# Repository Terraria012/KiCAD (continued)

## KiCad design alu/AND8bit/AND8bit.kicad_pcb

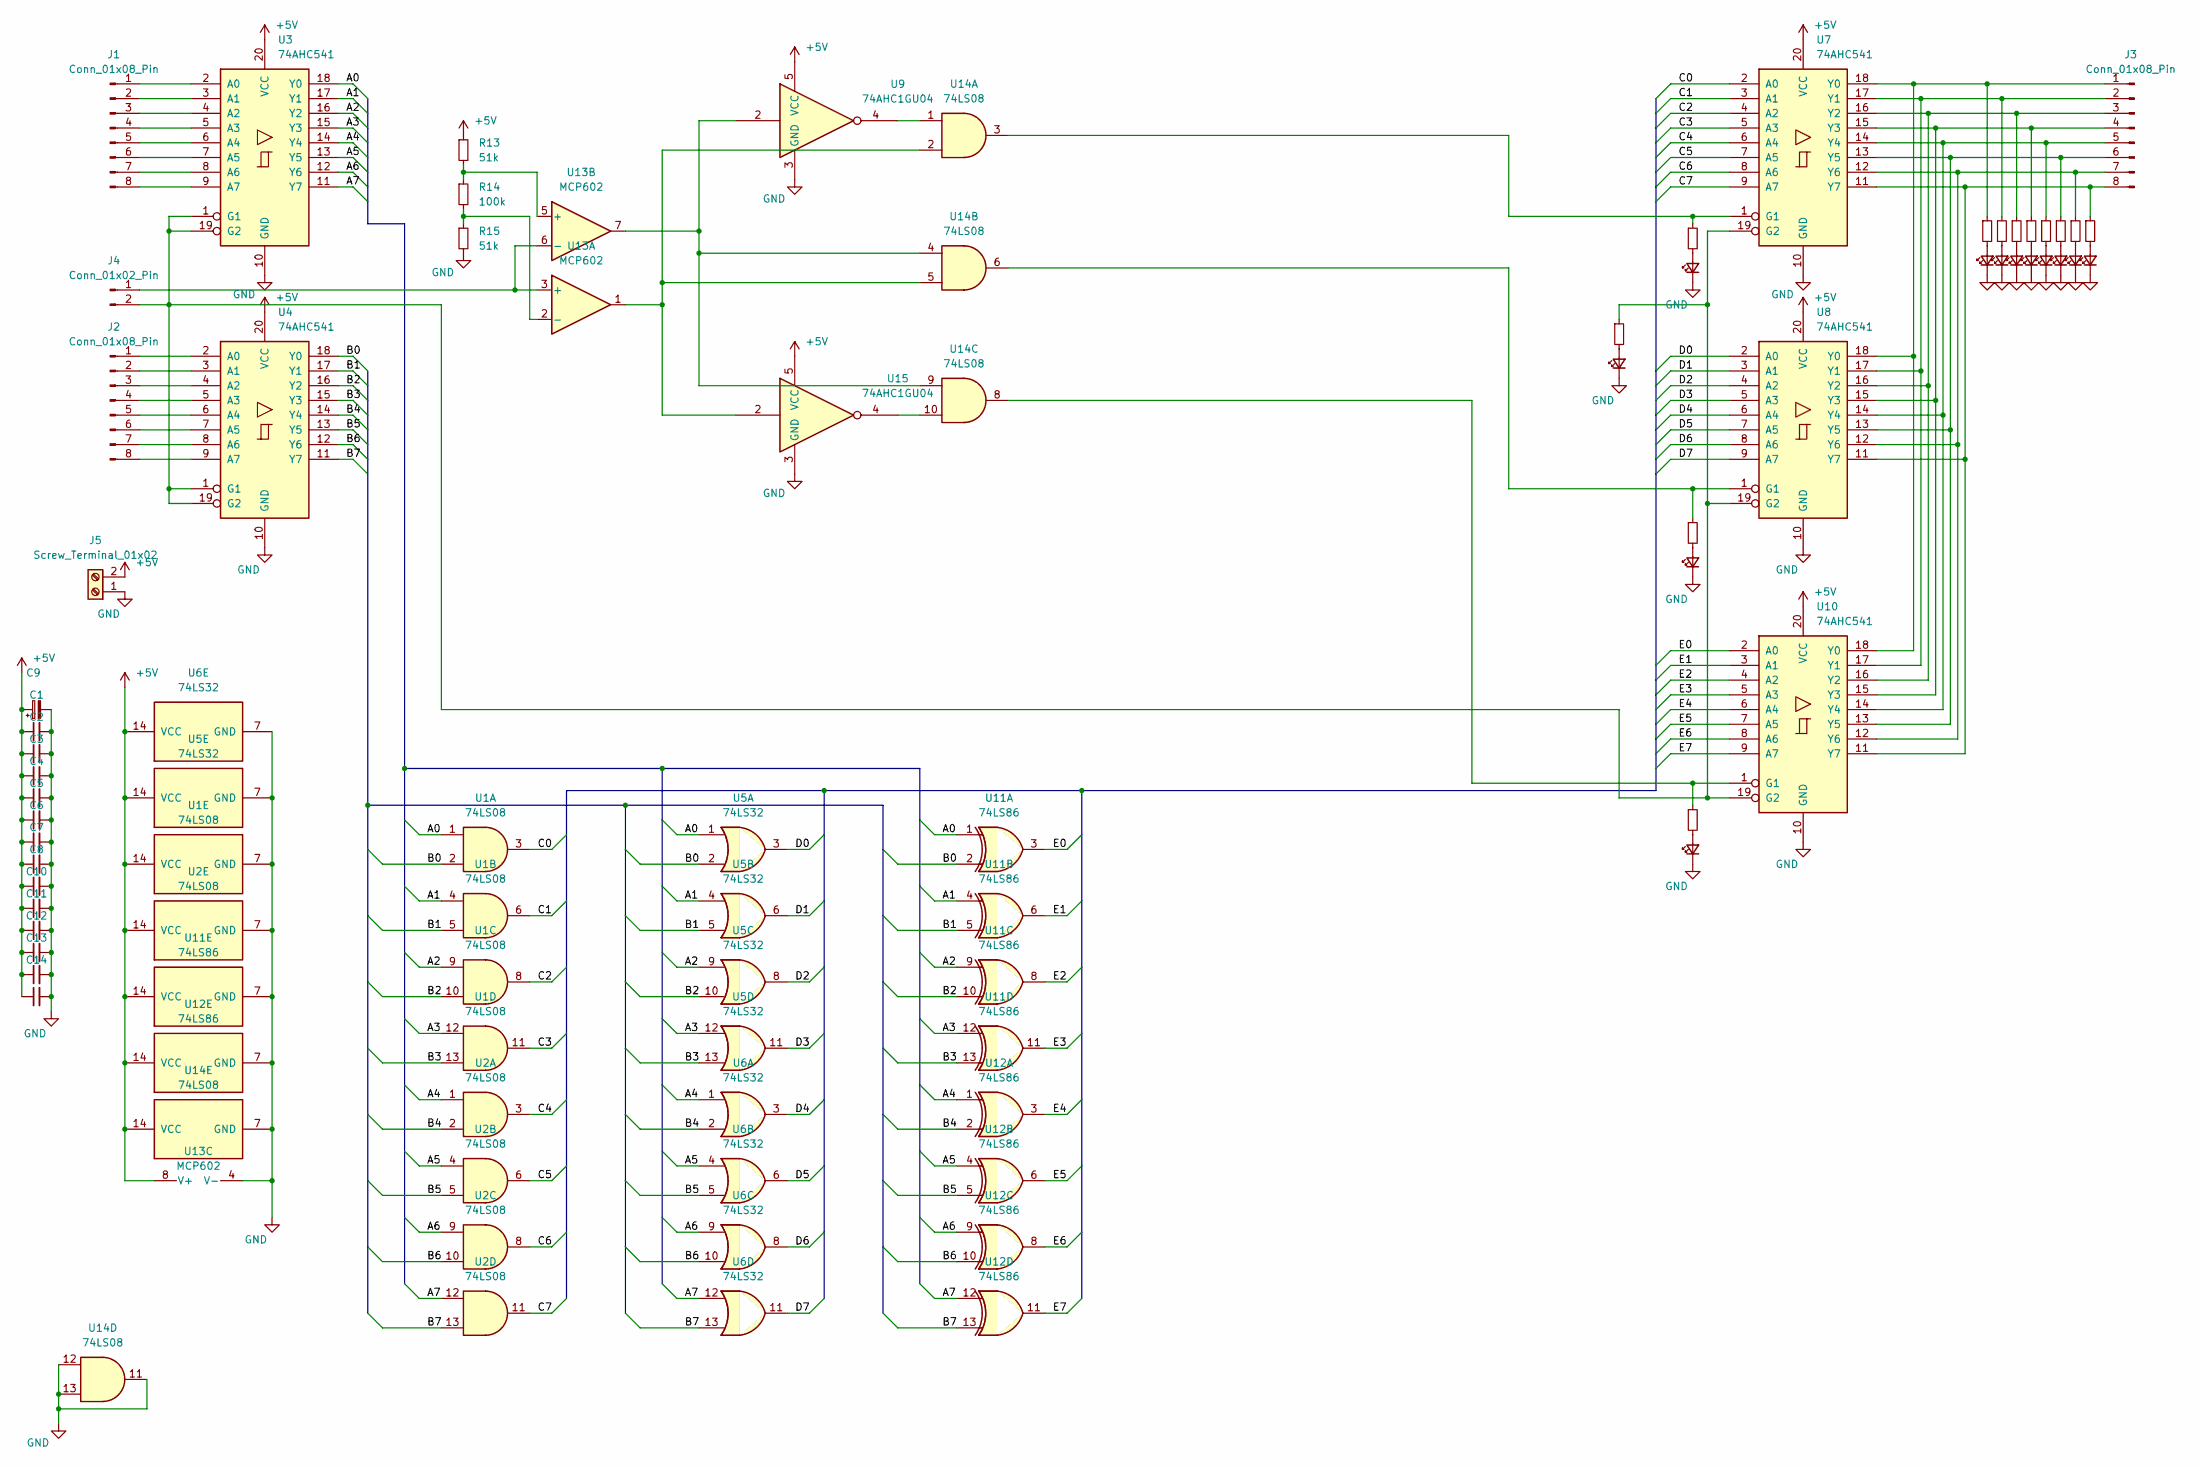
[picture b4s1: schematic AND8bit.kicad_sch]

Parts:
C1, C2, C3, C4, C5, C6, C7, C8, C10, C11, C12, C13, C14: C_Small; C_0603_1608Metric
C9: C_Polarized_Small; CP_Radial_D6.3mm_P2.50mm
D1, D2, D3, D4, D5, D6, D7, D8, D9, D10, D11, D12: LED_Small; LED_0603_1608Metric
J1, J2, J3: Conn_01x08_Pin; PinHeader_1x08_P2.54mm_Vertical
J4: Conn_01x02_Pin; PinHeader_1x02_P2.54mm_Vertical
J5: Screw_Terminal_01x02; TerminalBlock_bornier-2_P5.08mm
R1, R2, R3, R4, R5, R6, R7, R8, R9, R10, R11, R12: R_Small; R_0603_1608Metric
R13, R15: 51k; R_0603_1608Metric
R14: 100k; R_0603_1608Metric
U1, U2, U14: 74LS08; DIP-14_W7.62mm
U3, U4, U7, U8, U10: 74AHC541; DIP-20_W7.62mm
U5, U6: 74LS32; DIP-14_W7.62mm
U9, U15: 74AHC1GU04; ssop5-p-0.65a
U11, U12: 74LS86; DIP-14_W7.62mm
U13: MCP602; DIP-8_W7.62mm

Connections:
+5V: C1.1, C2.1, C3.1, C4.1, C5.1, C6.1, C7.1, C8.1, C9.1, C10.1, C11.1, C12.1, C13.1, C14.1, J5.2, R13.1, U1.14 (VCC), U2.14 (VCC), U3.20 (VCC), U4.20 (VCC), U5.14 (VCC), U6.14 (VCC), U7.20 (VCC), U8.20 (VCC), U9.5 (VCC), U10.20 (VCC), U11.14 (VCC), U12.14 (VCC), U13.8 (V+), U14.14 (VCC), U15.5 (VCC)
/A0: U1.1, U3.18 (Y0), U5.1, U11.1
/A1: U1.4, U3.17 (Y1), U5.4, U11.4
/A2: U1.9, U3.16 (Y2), U5.9, U11.9
/A3: U1.12, U3.15 (Y3), U5.12, U11.12
/A4: U2.1, U3.14 (Y4), U6.1, U12.1
/A5: U2.4, U3.13 (Y5), U6.4, U12.4
/A6: U2.9, U3.12 (Y6), U6.9, U12.9
/A7: U2.12, U3.11 (Y7), U6.12, U12.12
/B0: U1.2, U4.18 (Y0), U5.2, U11.2
/B1: U1.5, U4.17 (Y1), U5.5, U11.5
/B2: U1.10, U4.16 (Y2), U5.10, U11.10
/B3: U1.13, U4.15 (Y3), U5.13, U11.13
/B4: U2.2, U4.14 (Y4), U6.2, U12.2
/B5: U2.5, U4.13 (Y5), U6.5, U12.5
/B6: U2.10, U4.12 (Y6), U6.10, U12.10
/B7: U2.13, U4.11 (Y7), U6.13, U12.13
/C0: U1.3, U7.2 (A0)
/C1: U1.6, U7.3 (A1)
/C2: U1.8, U7.4 (A2)
/C3: U1.11, U7.5 (A3)
/C4: U2.3, U7.6 (A4)
/C5: U2.6, U7.7 (A5)
/C6: U2.8, U7.8 (A6)
/C7: U2.11, U7.9 (A7)
/D0: U5.3, U8.2 (A0)
/D1: U5.6, U8.3 (A1)
/D2: U5.8, U8.4 (A2)
/D3: U5.11, U8.5 (A3)
/D4: U6.3, U8.6 (A4)
/D5: U6.6, U8.7 (A5)
/D6: U6.8, U8.8 (A6)
/D7: U6.11, U8.9 (A7)
/E0: U10.2 (A0), U11.3
/E1: U10.3 (A1), U11.6
/E2: U10.4 (A2), U11.8
/E3: U10.5 (A3), U11.11
/E4: U10.6 (A4), U12.3
/E5: U10.7 (A5), U12.6
/E6: U10.8 (A6), U12.8
/E7: U10.9 (A7), U12.11
GND: C1.2, C2.2, C3.2, C4.2, C5.2, C6.2, C7.2, C8.2, C9.2, C10.2, C11.2, C12.2, C13.2, C14.2, D1.1 (K), D2.1 (K), D3.1 (K), D4.1 (K), D5.1 (K), D6.1 (K), D7.1 (K), D8.1 (K), D9.1 (K), D10.1 (K), D11.1 (K), D12.1 (K), J5.1, R15.2, U1.7 (GND), U2.7 (GND), U3.10 (GND), U4.10 (GND), U5.7 (GND), U6.7 (GND), U7.10 (GND), U8.10 (GND), U9.3 (GND), U10.10 (GND), U11.7 (GND), U12.7 (GND), U13.4 (V-), U14.7 (GND), U14.11, U14.12, U14.13, U15.3 (GND)
unnamed: D1.2 (A), R1.2
unnamed: D2.2 (A), R2.2
unnamed: D3.2 (A), R3.2
unnamed: D4.2 (A), R4.2
unnamed: D5.2 (A), R5.2
unnamed: D6.2 (A), R6.2
unnamed: D7.2 (A), R7.2
unnamed: D8.2 (A), R8.2
unnamed: D9.2 (A), R9.2
unnamed: D10.2 (A), R10.2
unnamed: D11.2 (A), R11.2
unnamed: D12.2 (A), R12.2
unnamed: J1.1, U3.2 (A0)
unnamed: J1.2, U3.3 (A1)
unnamed: J1.3, U3.4 (A2)
unnamed: J1.4, U3.5 (A3)
unnamed: J1.5, U3.6 (A4)
unnamed: J1.6, U3.7 (A5)
unnamed: J1.7, U3.8 (A6)
unnamed: J1.8, U3.9 (A7)
unnamed: J2.1, U4.2 (A0)
unnamed: J2.2, U4.3 (A1)
unnamed: J2.3, U4.4 (A2)
unnamed: J2.4, U4.5 (A3)
unnamed: J2.5, U4.6 (A4)
unnamed: J2.6, U4.7 (A5)
unnamed: J2.7, U4.8 (A6)
unnamed: J2.8, U4.9 (A7)
unnamed: J3.1, R4.1, U7.18 (Y0), U8.18 (Y0), U10.18 (Y0)
unnamed: J3.2, R5.1, U7.17 (Y1), U8.17 (Y1), U10.17 (Y1)
unnamed: J3.3, R6.1, U7.16 (Y2), U8.16 (Y2), U10.16 (Y2)
unnamed: J3.4, R7.1, U7.15 (Y3), U8.15 (Y3), U10.15 (Y3)
unnamed: J3.5, R8.1, U7.14 (Y4), U8.14 (Y4), U10.14 (Y4)
unnamed: J3.6, R9.1, U7.13 (Y5), U8.13 (Y5), U10.13 (Y5)
unnamed: J3.7, R10.1, U7.12 (Y6), U8.12 (Y6), U10.12 (Y6)
unnamed: J3.8, R11.1, U7.11 (Y7), U8.11 (Y7), U10.11 (Y7)
unnamed: J4.1, U13.3 (+), U13.6 (-)
unnamed: J4.2, R1.1, U3.1 (G1), U3.19 (G2), U4.1 (G1), U4.19 (G2), U7.19 (G2), U8.19 (G2), U10.19 (G2)
unnamed: R3.1, U7.1 (G1), U14.3
unnamed: R2.1, U8.1 (G1), U14.6
unnamed: R12.1, U10.1 (G1), U14.8
unnamed: U13.1, U14.2, U14.5, U15.2
unnamed: U9.2, U13.7, U14.4, U14.9
unnamed: R14.2, R15.1, U13.2 (-)
unnamed: R13.2, R14.1, U13.5 (+)
unnamed: U9.4, U14.1
unnamed: U14.10, U15.4

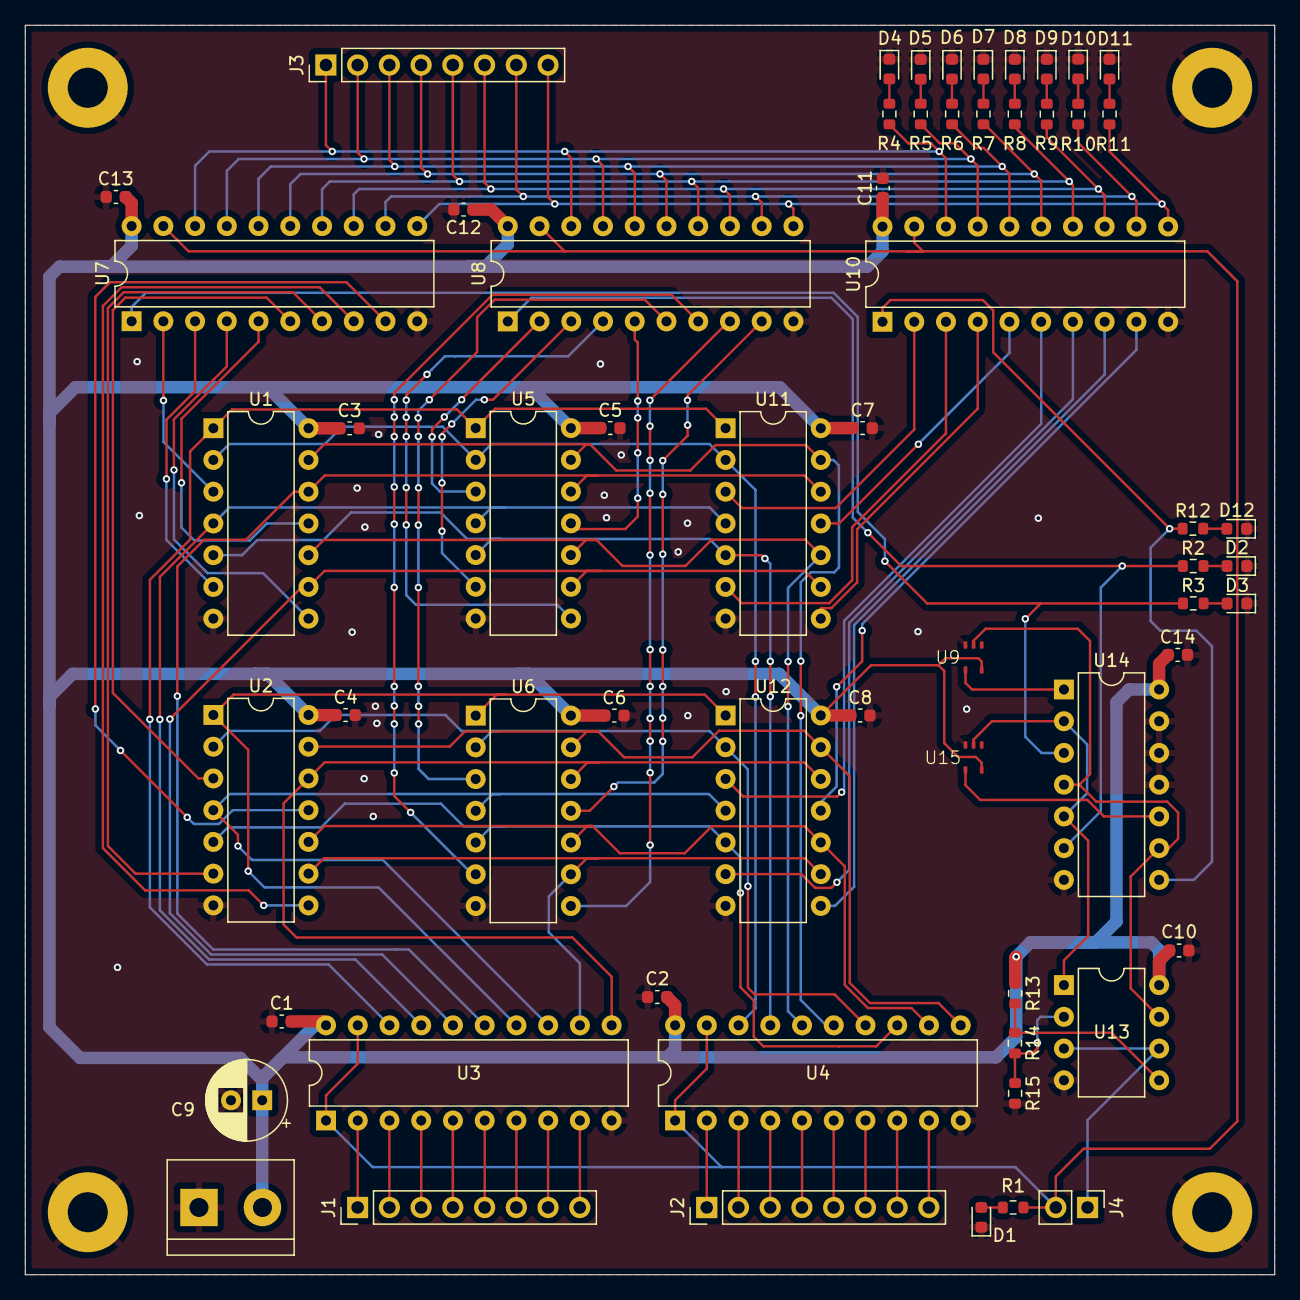
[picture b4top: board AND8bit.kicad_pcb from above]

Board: 2 copper layers, 100.0 x 100.0 mm, 61 parts (0 on the bottom side), 89 nets.

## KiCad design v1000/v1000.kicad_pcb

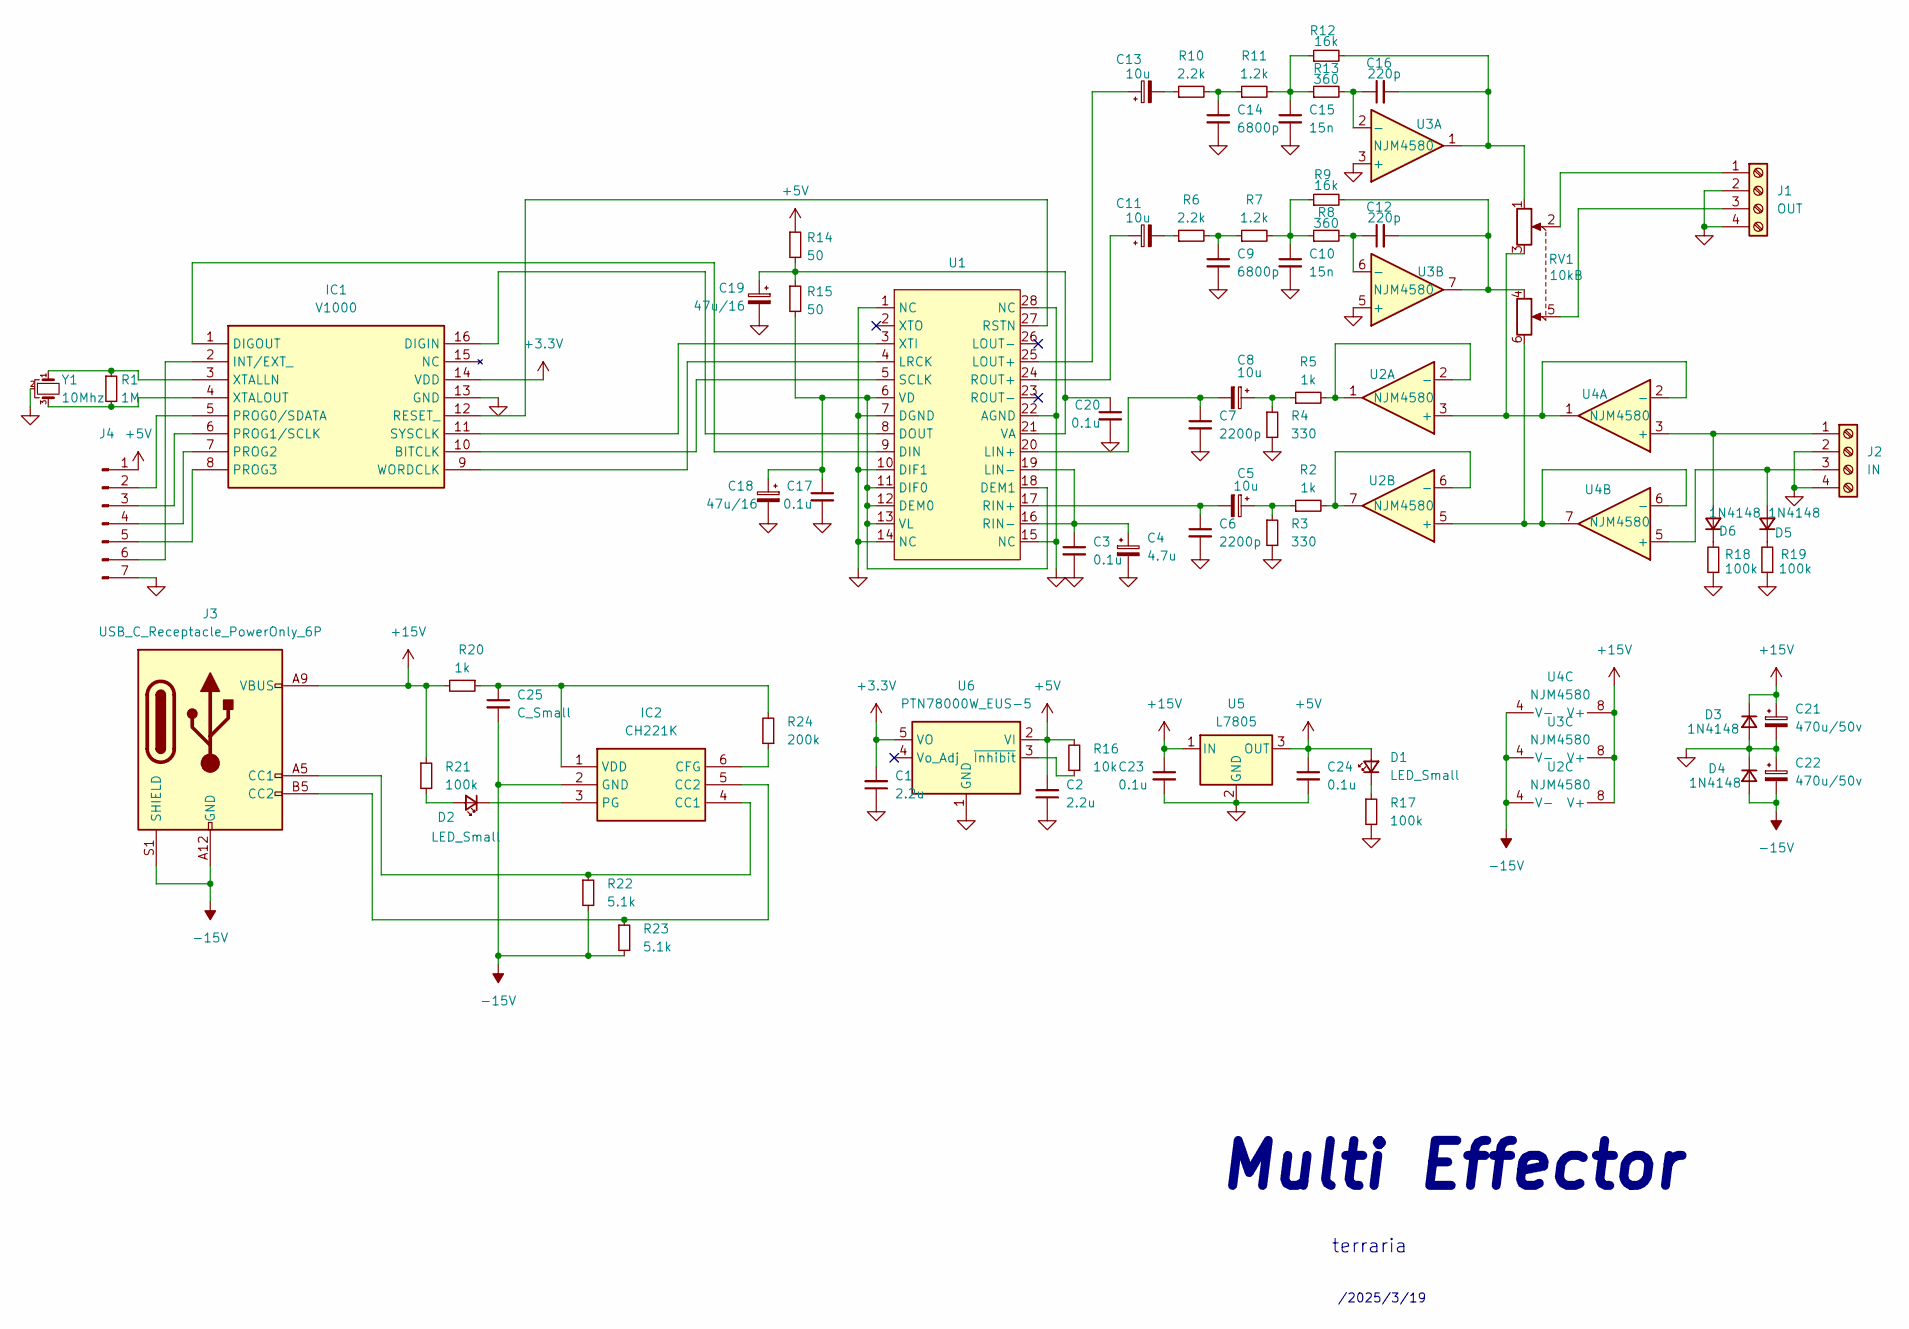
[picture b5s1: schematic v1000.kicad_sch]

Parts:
C1, C2: 2.2u; C_0603_1608Metric_Pad1.08x0.95mm_HandSolder
C3, C17, C20, C23, C24: 0.1u; C_0603_1608Metric_Pad1.08x0.95mm_HandSolder
C4: 4.7u; CP_Radial_D5.0mm_P2.00mm
C5, C8, C11, C13: 10u; CP_Radial_D5.0mm_P2.00mm
C6, C7: 2200p; C_0603_1608Metric_Pad1.08x0.95mm_HandSolder
C9, C14: 6800p; C_0603_1608Metric_Pad1.08x0.95mm_HandSolder
C10, C15: 15n; C_0603_1608Metric_Pad1.08x0.95mm_HandSolder
C12, C16: 220p; C_0603_1608Metric_Pad1.08x0.95mm_HandSolder
C18, C19: 47u/16; CP_Radial_D6.3mm_P2.50mm
C21, C22: 470u/50v; CP_Radial_D10.0mm_P5.00mm
C25: C_Small; C_0603_1608Metric
D1, D2: LED_Small; LED_0603_1608Metric_Pad1.05x0.95mm_HandSolder
D3, D4, D5, D6: 1N4148; D_SOD-123
IC1: V1000; SOIC127P1034X250-16N; Manufacturer_Part_Number V1000
IC2: CH221K; SOT95P280X120-6N; Manufacturer_Part_Number CH221K
J1: OUT; TerminalBlock_TE_282834-4_1x04_P2.54mm_Horizontal
J2: IN; TerminalBlock_TE_282834-4_1x04_P2.54mm_Horizontal
J3: USB_C_Receptacle_PowerOnly_6P; USB_C_Receptacle_GCT_USB4125-xx-x_6P_TopMnt_Horizontal
J4: Conn_01x07_Pin; PinSocket_1x07_P2.54mm_Vertical
R1: 1M; R_0603_1608Metric_Pad0.98x0.95mm_HandSolder
R2, R5, R20: 1k; R_0603_1608Metric_Pad0.98x0.95mm_HandSolder
R3, R4: 330; R_0603_1608Metric_Pad0.98x0.95mm_HandSolder
R6, R10: 2.2k; R_0603_1608Metric_Pad0.98x0.95mm_HandSolder
R7, R11: 1.2k; R_0603_1608Metric_Pad0.98x0.95mm_HandSolder
R8, R13: 360; R_0603_1608Metric_Pad0.98x0.95mm_HandSolder
R9, R12: 16k; R_0603_1608Metric_Pad0.98x0.95mm_HandSolder
R14, R15: 50; R_0603_1608Metric_Pad0.98x0.95mm_HandSolder
R16: 10k; R_0603_1608Metric_Pad0.98x0.95mm_HandSolder
R17, R18, R19, R21: 100k; R_0603_1608Metric_Pad0.98x0.95mm_HandSolder
R22, R23: 5.1k; R_0603_1608Metric_Pad0.98x0.95mm_HandSolder
R24: 200k; R_0603_1608Metric_Pad0.98x0.95mm_HandSolder
RV1: 10kB; Potentiometer_Alps_RK097_Dual_Horizontal_ver_terraria
U1: SSOP-28_5.3x10.2mm_P0.65mm
U2, U3, U4: NJM4580; SIP-8_19x3mm_P2.54mm
U5: L7805; TO-252-3_TabPin2
U6: PTN78000W_EUS-5; TSOT-23-5
Y1: 10Mhz; PinHeader_1x03_P2.54mm_Vertical

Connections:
+3.3V: C1.2, IC1.14 (VDD), U6.5 (VO)
+5V: C2.2, C24.1, D1.2 (A), J4.1, R14.1, R16.2, U5.3 (OUT), U6.2 (VI)
+15V: C21.1, C23.1, D3.1 (K), J3.A9 (VBUS), J3.B9 (VBUS), R20.2, R21.1, U2.8 (V+), U3.8 (V+), U4.8 (V+), U5.1 (IN)
-15V: C22.2, C25.2, D4.2 (A), IC2.2 (GND), J3.A12 (GND), J3.B12 (GND), J3.S1 (SHIELD), R22.2, R23.2, U2.4 (V-), U3.4 (V-), U4.4 (V-)
unnamed: C5.1, R2.1, R3.1
unnamed: C8.1, R4.1, R5.1
unnamed: C9.1, R6.2, R7.1
unnamed: C10.1, R7.2, R8.1, R9.1
unnamed: C11.2, R6.1
unnamed: C12.2, R9.2, RV1.4, U3.7
unnamed: C13.2, R10.1
unnamed: C14.1, R10.2, R11.1
unnamed: C15.1, R11.2, R12.1, R13.1
unnamed: C16.2, R12.2, RV1.1, U3.1
unnamed: D1.1 (K), R17.1
unnamed: D2.2 (A), R21.2
unnamed: D2.1 (K), IC2.3 (PG)
unnamed: D5.2 (A), J2.3, U4.5 (+)
unnamed: D5.1 (K), R19.2
unnamed: D6.2 (A), J2.1, U4.3 (+)
unnamed: D6.1 (K), R18.2
unnamed: IC1.10 (BITCLK), U1.5 (SCLK)
unnamed: IC1.16 (DIGIN), U1.8 (DOUT)
unnamed: IC1.1 (DIGOUT), U1.9 (DIN)
unnamed: IC1.2 (INT/EXT_), J4.6
unnamed: IC1.5 (PROG0/SDATA), J4.2
unnamed: IC1.6 (PROG1/SCLK), J4.3
unnamed: IC1.7 (PROG2), J4.4
unnamed: IC1.8 (PROG3), J4.5
unnamed: IC1.12 (RESET_), U1.27 (RSTN)
unnamed: IC1.11 (SYSCLK), U1.3 (XTI)
unnamed: IC1.9 (WORDCLK), U1.4 (LRCK)
unnamed: IC1.3 (XTALLN), R1.1, Y1.1
unnamed: IC1.4 (XTALOUT), R1.2, Y1.3
unnamed: IC2.4 (CC1), J3.A5 (CC1), R22.1
unnamed: IC2.5 (CC2), J3.B5 (CC2), R23.1
unnamed: IC2.6 (CFG), R24.1
unnamed: C25.1, IC2.1 (VDD), R20.1, R24.2
unnamed: J1.1, RV1.2
unnamed: J1.3, RV1.5
unnamed: C17.1, C18.1, R15.2, U1.6 (VD), U1.11 (DIF0), U1.12 (DEM0), U1.13 (VL), U1.18 (DEM1)
unnamed: C7.1, C8.2, U1.20 (LIN+)
unnamed: C3.1, C4.1, U1.16 (RIN-), U1.19 (LIN-)
unnamed: C13.1, U1.25 (LOUT+)
unnamed: C5.2, C6.1, U1.17 (RIN+)
unnamed: C11.1, U1.24 (ROUT+)
unnamed: C19.1, C20.1, R14.2, R15.1, U1.21 (VA)
unnamed: RV1.3, U2.3 (+), U4.1, U4.2 (-)
unnamed: R5.2, U2.1, U2.2 (-)
unnamed: RV1.6, U2.5 (+), U4.6 (-), U4.7
unnamed: R2.2, U2.6 (-), U2.7
unnamed: C16.1, R13.2, U3.2 (-)
unnamed: C12.1, R8.2, U3.6 (-)
unnamed: R16.1, U6.3 (~Inhibit)

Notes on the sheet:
Multi Effector
terraria
/2025/3/19

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
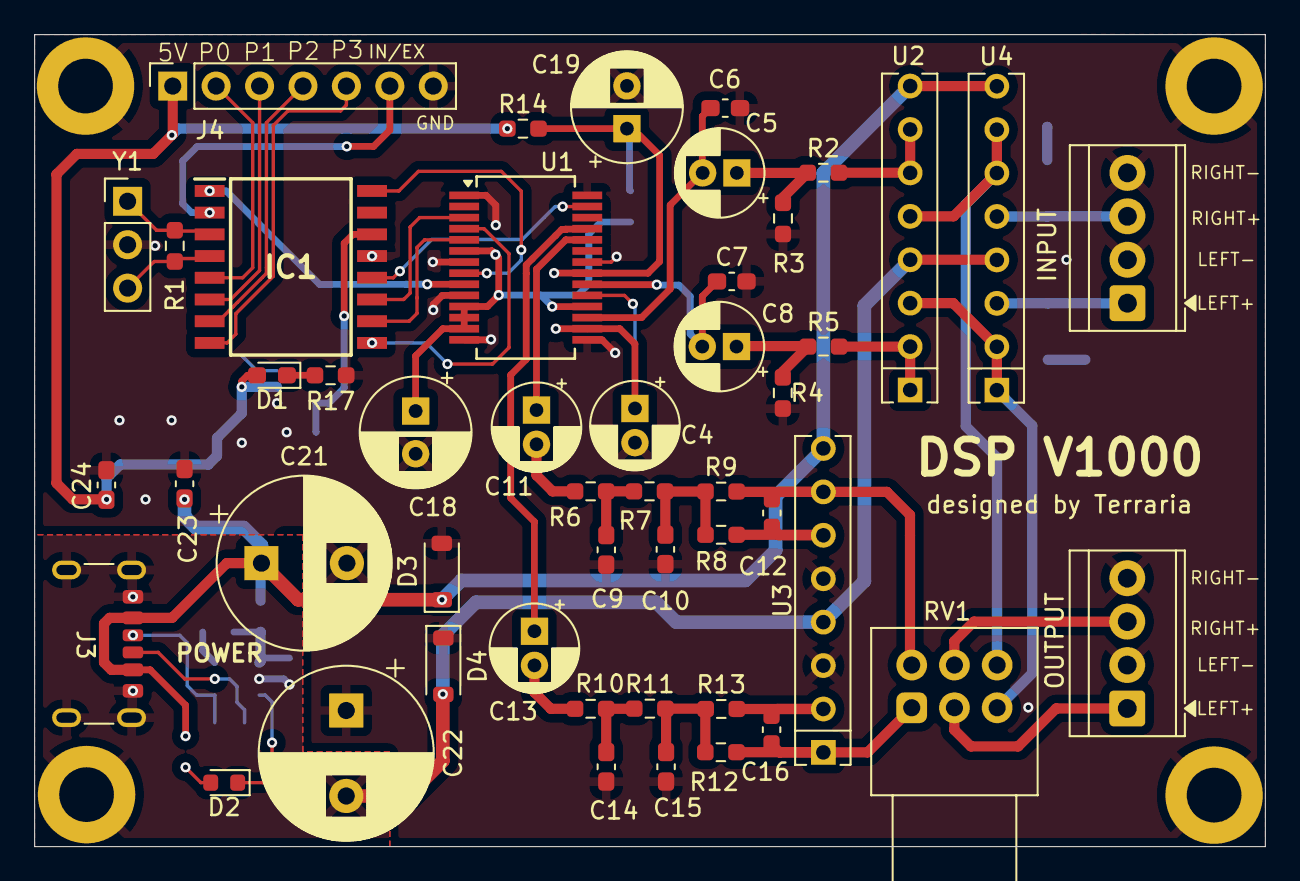
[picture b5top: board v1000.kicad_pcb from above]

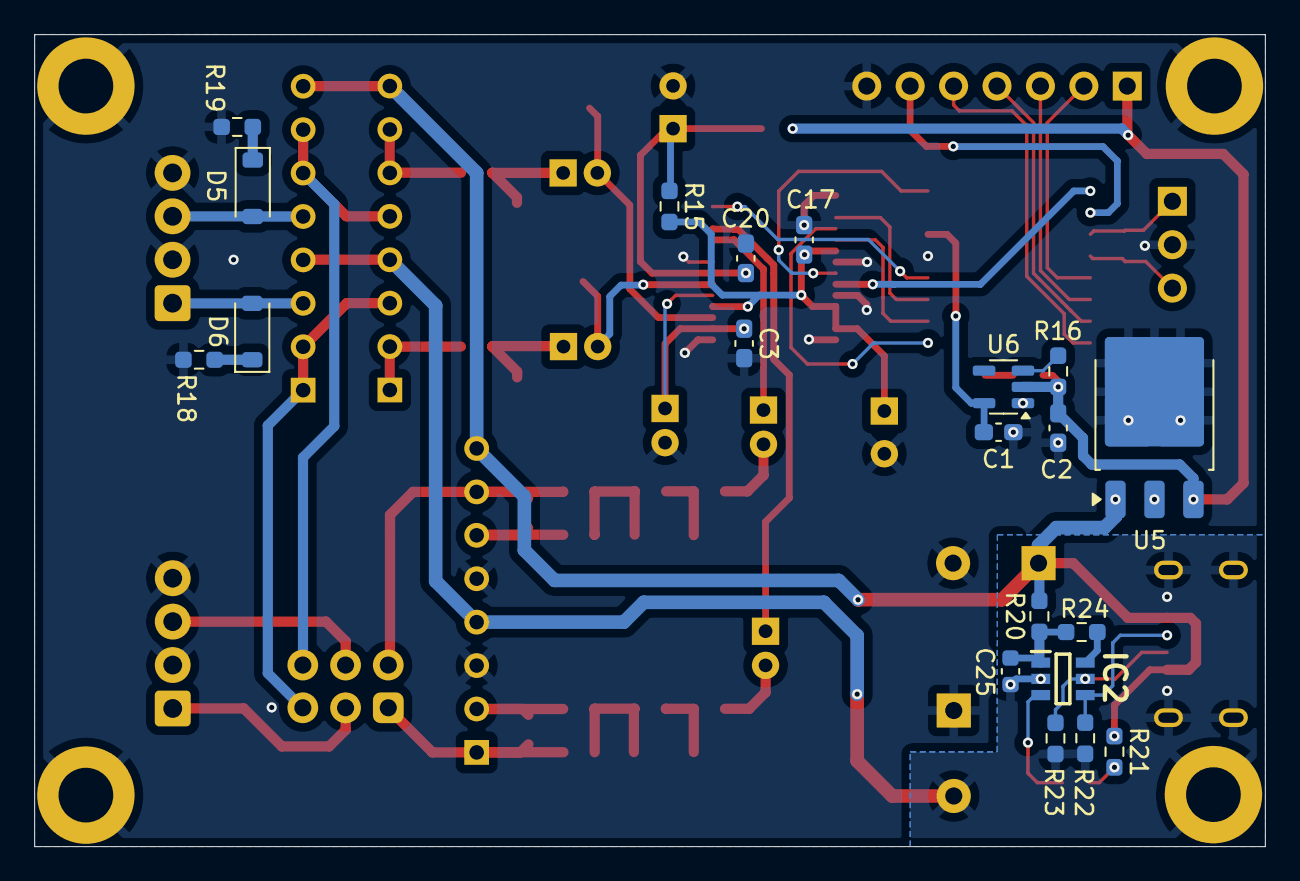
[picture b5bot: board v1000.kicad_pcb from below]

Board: 2 copper layers, 72.0 x 47.5 mm, 69 parts (20 on the bottom side), 55 nets.

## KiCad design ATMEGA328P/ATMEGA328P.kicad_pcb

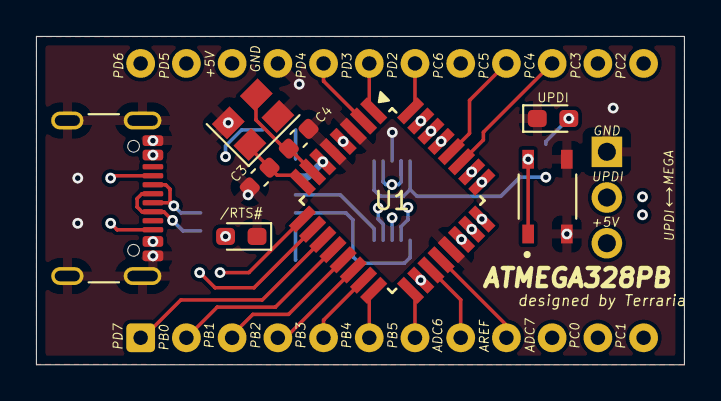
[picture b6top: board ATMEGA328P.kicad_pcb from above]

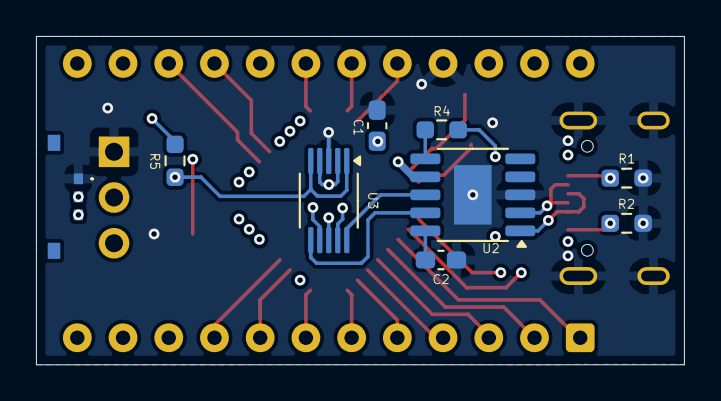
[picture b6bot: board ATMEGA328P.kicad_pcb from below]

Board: 4 copper layers, 36.0 x 18.2 mm, 19 parts (9 on the bottom side), 40 nets.

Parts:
/RTS#: LED_Small; LED_0603_1608Metric_Pad1.05x0.95mm_HandSolder
C1, C2: 0.1u; C_0603_1608Metric_Pad1.08x0.95mm_HandSolder
C3, C4: 22p; C_0603_1608Metric
J1: USB_C_Receptacle_USB2.0_16P; USB_C_Receptacle_GCT_USB4105-xx-A_16P_TopMnt_Horizontal
J2: Conn_02x12_Counter_Clockwise; DIP-24_W15.24mm
J3: Conn_01x03_Pin; PinHeader_1x03_P2.54mm_Vertical
R1, R2: 5.1k; R_0603_1608Metric_Pad0.98x0.95mm_HandSolder
R4, R5: 10k; R_0603_1608Metric_Pad0.98x0.95mm_HandSolder
SW1: SW_MEC_5E; SW_SKRPABE010
SW2: SSAJ120100
U1: ATmega328P-A; TQFP-32_7x7mm_P0.8mm
U2: CH340K; SSOP-10-1EP_3.9x4.9mm_P1mm_EP2.1x3.3mm
U3: TS5A23159DGS; VSSOP-10_3x3mm_P0.5mm
UPDI: LED_Small; LED_0603_1608Metric_Pad1.05x0.95mm_HandSolder
Y1: 16MHz; Crystal_SMD_3225-4Pin_3.2x2.5mm

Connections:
+5V: C1.1, J1.A4 (VBUS), J1.A9 (VBUS), J1.B4 (VBUS), J1.B9 (VBUS), J2.22, J3.3, SW2.2 (MP2), U1.4 (VCC), U1.6 (VCC), U1.18 (AVCC), U2.7 (VCC), U3.8 (VCC)
/PB0: J2.2, U1.12 (PB0)
/PB1: J2.3, U1.13 (PB1)
/PB2: J2.4, U1.14 (PB2)
/PB3: J2.5, U1.15 (PB3)
/PB4: J2.6, U1.16 (PB4)
/PB5: J2.7, U1.17 (PB5)
/PC0: J2.11, U1.23 (PC0)
/PC1: J2.12, U1.24 (PC1)
/PC2: J2.13, U1.25 (PC2)
/PC3: J2.14, U1.26 (PC3)
/PC4: J2.15, U1.27 (PC4)
/PC5: J2.16, U1.28 (PC5)
/PD2: J2.18, U1.32 (PD2)
/PD3: J2.19, U1.1 (PD3)
/PD4: J2.20, U1.2 (PD4)
/PD5: J2.23, U1.9 (PD5)
/PD6: J2.24, U1.10 (PD6)
/PD7: J2.1, U1.11 (PD7)
ADC6: J2.8, U1.19 (ADC6)
ADC7: J2.10, U1.22 (ADC7)
AREF: J2.9, U1.20 (AREF)
D+: J1.A6 (D+), J1.B6 (D+), U2.1 (UD+)
D-: J1.A7 (D-), J1.B7 (D-), U2.2 (UD-)
GND: /RTS#.1 (K), C1.2, C2.2, C3.2, C4.1, J1.A1 (GND), J1.A12 (GND), J1.B1 (GND), J1.B12 (GND), J1.S1 (SHIELD), J2.21, J3.1, R1.2, R2.2, SW1.3 (K), SW1.4 (A), SW2.1 (MP1), U1.3 (GND), U1.5 (GND), U1.21 (GND), U2.3 (GND), U2.11 (GND), U3.3 (GND), UPDI.1 (K), Y1.2, Y1.4
unnamed: /RTS#.2 (A), R4.2
unnamed: R5.2, UPDI.2 (A)
unnamed: J1.A5 (CC1), R1.1
unnamed: J1.B5 (CC2), R2.1
unnamed: R5.1, SW2.3 (COM), U3.1, U3.5
unnamed: C4.2, U1.7 (XTAL1/PB6), Y1.3
unnamed: C3.1, U1.8 (XTAL2/PB7), Y1.1
unnamed: C2.1, U2.10 (V3)
PC6: J2.17, SW1.1, SW1.2, U1.29 (~RESET/PC6)
PD0/RxD: U1.30 (PD0), U3.7
PD1/TxD: U1.31 (PD1), U3.9
RTS#: R4.1, U2.6 (~RTS)
RxD: U2.9 (RXD), U3.6
TxD: U2.8 (TXD), U3.10
UPDI: J3.2, U3.2, U3.4

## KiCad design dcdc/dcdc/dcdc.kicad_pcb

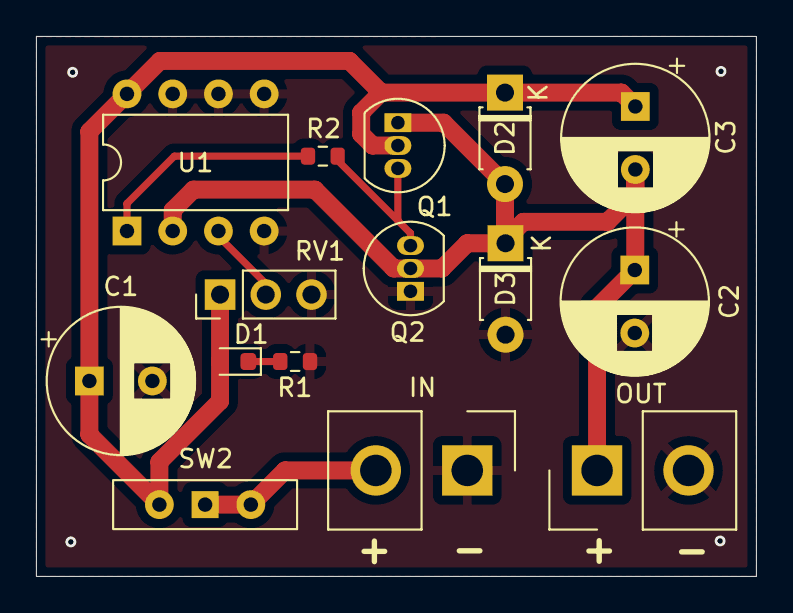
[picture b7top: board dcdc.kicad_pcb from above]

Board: 2 copper layers, 40.0 x 30.0 mm, 15 parts (0 on the bottom side), 8 nets.

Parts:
C1, C2, C3: 100u; CP_Radial_D8.0mm_P3.50mm
D1: LED; D_0603_1608Metric
D2, D3: 1N60; D_T-1_P5.08mm_Horizontal
IN: Screw_Terminal_01x02; Samtec_HPM-02-05-x-S_Straight_1x02_Pitch5.08mm
OUT: Screw_Terminal_01x02; Samtec_HPM-02-05-x-S_Straight_1x02_Pitch5.08mm
Q1: 2SC1815; TO-92_Inline
Q2: 2SA1015; TO-92_Inline
R1: 100k; R_0603_1608Metric
R2: 220; R_0603_1608Metric
RV1: 100k; PinHeader_1x03_P2.54mm_Vertical
SW2: SW_Wuerth_450301014042; SW_Slide-03_Wuerth-WS-SLTV_10x2.5x6.4_P2.54mm
U1: LM358; DIP-8_W7.62mm

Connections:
GND: C1.2, C2.2, D3.2 (A), IN.1, OUT.2, Q2.1 (E), R1.2, RV1.3, U1.4 (V-), U1.5 (+), U1.6 (-), U1.7
unnamed: D1.1 (K), R1.1
unnamed: C2.1, C3.2, D2.2 (A), D3.1 (K), OUT.1, Q1.1 (E), Q2.2 (C), U1.2 (-)
unnamed: IN.2, SW2.1 (B), SW2.2 (C)
unnamed: Q1.3 (B), Q2.3 (B), R2.2
unnamed: R2.1, U1.1
unnamed: RV1.2, U1.3 (+)
VBUS: C1.1, C3.1, D1.2 (A), D2.1 (K), Q1.2 (C), RV1.1, SW2.3 (A), U1.8 (V+)

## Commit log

2025-05-26 1回目のコミット
2025-05-26 2回目のコミット
